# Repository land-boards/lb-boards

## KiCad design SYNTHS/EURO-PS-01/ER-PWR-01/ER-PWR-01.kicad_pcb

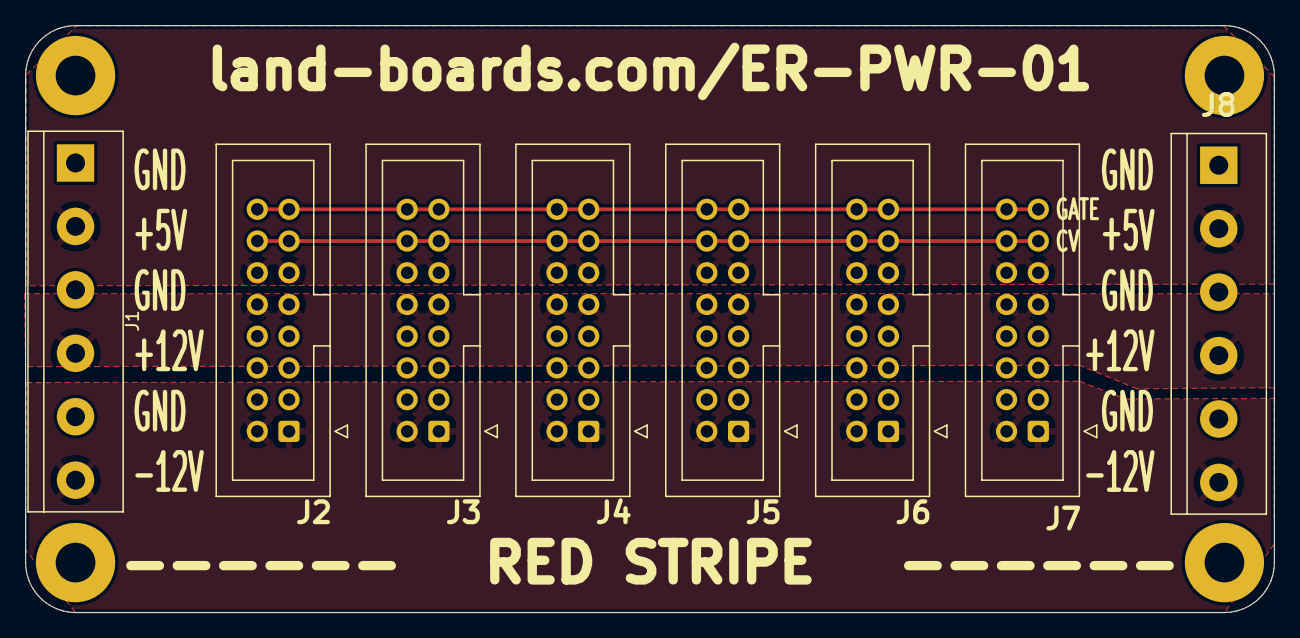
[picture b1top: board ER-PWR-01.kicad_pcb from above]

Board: 2 copper layers, 100.0 x 47.0 mm, 12 parts (0 on the bottom side), 6 nets.

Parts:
J1, J8: Conn_01x06; TerminalBlock_bornier-6_P5.08mm
J2, J3, J4, J5, J6, J7: Conn_02x08_Odd_Even; IDC-Header_2x08_P2.54mm_Vertical
MTG1, MTG2, MTG3, MTG4: MountingHole; MTG-4-40

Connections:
/+5V: J1.2, J2.11, J2.12, J3.11, J3.12, J4.11, J4.12, J5.11, J5.12, J6.11, J6.12, J7.11, J7.12, J8.2
/+12V: J1.4, J2.9, J2.10, J3.9, J3.10, J4.9, J4.10, J5.9, J5.10, J6.9, J6.10, J7.9, J7.10, J8.4
/-12V: J1.6, J2.1, J2.2, J3.1, J3.2, J4.1, J4.2, J5.1, J5.2, J6.1, J6.2, J7.1, J7.2, J8.6
/GND: J1.1, J1.3, J1.5, J2.3, J2.4, J2.5, J2.6, J2.7, J2.8, J3.3, J3.4, J3.5, J3.6, J3.7, J3.8, J4.3, J4.4, J4.5, J4.6, J4.7, J4.8, J5.3, J5.4, J5.5, J5.6, J5.7, J5.8, J6.3, J6.4, J6.5, J6.6, J6.7, J6.8, J7.3, J7.4, J7.5, J7.6, J7.7, J7.8, J8.1, J8.3, J8.5
/P13: J2.13, J2.14, J3.13, J3.14, J4.13, J4.14, J5.13, J5.14, J6.13, J6.14, J7.13, J7.14
/P15: J2.15, J2.16, J3.15, J3.16, J4.15, J4.16, J5.15, J5.16, J6.15, J6.16, J7.15, J7.16

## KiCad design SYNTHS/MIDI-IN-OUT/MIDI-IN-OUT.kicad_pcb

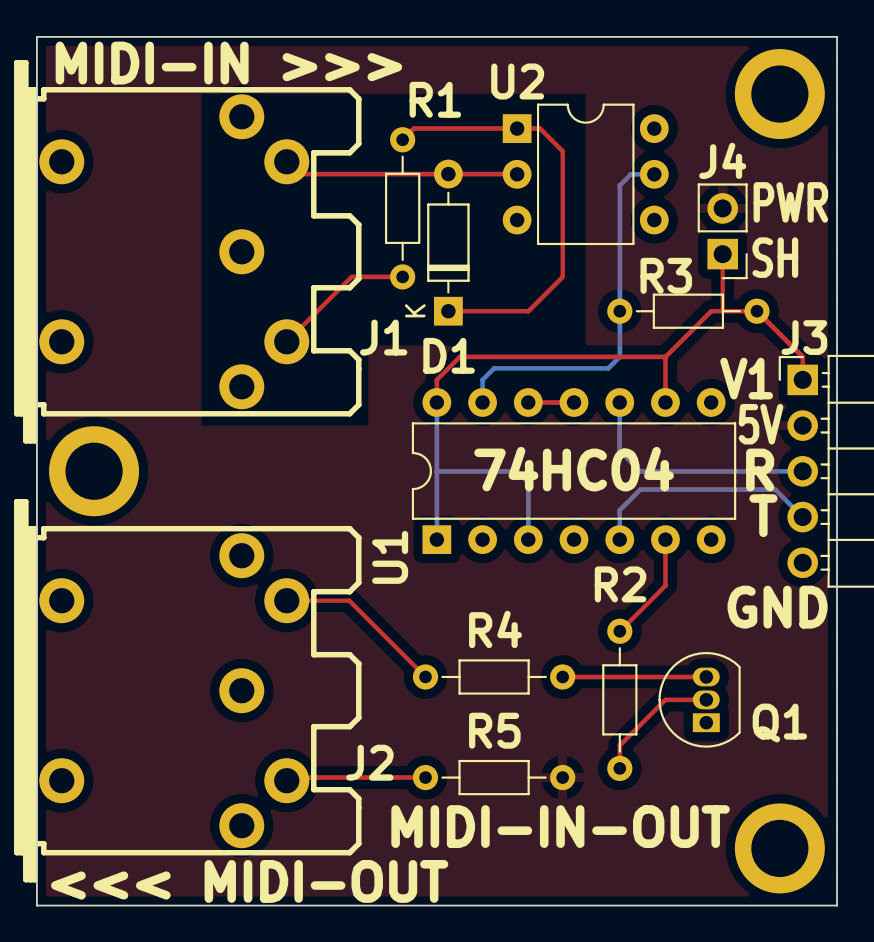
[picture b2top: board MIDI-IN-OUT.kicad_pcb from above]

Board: 2 copper layers, 44.4 x 48.3 mm, 16 parts (0 on the bottom side), 15 nets.

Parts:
D1: BAT41; D_DO-35_SOD27_P7.62mm_Horizontal
J1, J2: DIN-5; MIDI_DIN-5
J3: Conn_01x05; PinHeader_1x05_P2.54mm_Horizontal
J4: Conn_01x02; PinHeader_1x02_P2.54mm_Vertical
MTG1, MTG2, MTG3: MountingHole; MTG-4-40-SMALL
Q1: 2N3904; TO-92_Inline
R1, R4, R5: 220; R_Axial_DIN0204_L3.6mm_D1.6mm_P7.62mm_Horizontal
R2: 10K; R_Axial_DIN0204_L3.6mm_D1.6mm_P7.62mm_Horizontal
R3: 1K; R_Axial_DIN0204_L3.6mm_D1.6mm_P7.62mm_Horizontal
U1: 74HC04; DIP-14_W7.62mm
U2: 4N26; DIP-6_W7.62mm

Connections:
+3V3: J3.1, J4.1, R3.2, U1.1, U1.3, U1.9, U1.14 (VCC)
+5V: J3.2, J4.2, R5.2
/MIDI_IN: J1.4, R1.1
/RX: J3.3, U1.10
/TX: J3.4, U1.5
GND: J2.2, J3.5, Q1.1 (E), U1.7 (GND), U2.4
unnamed: D1.1 (K), R1.2, U2.1
unnamed: D1.2 (A), J1.5, U2.2
unnamed: J2.4, R5.1
unnamed: J2.5, R4.2
unnamed: Q1.2 (B), R2.1
unnamed: Q1.3 (C), R4.1
unnamed: R2.2, U1.6
unnamed: R3.1, U1.13, U2.5
unnamed: U1.11, U1.12

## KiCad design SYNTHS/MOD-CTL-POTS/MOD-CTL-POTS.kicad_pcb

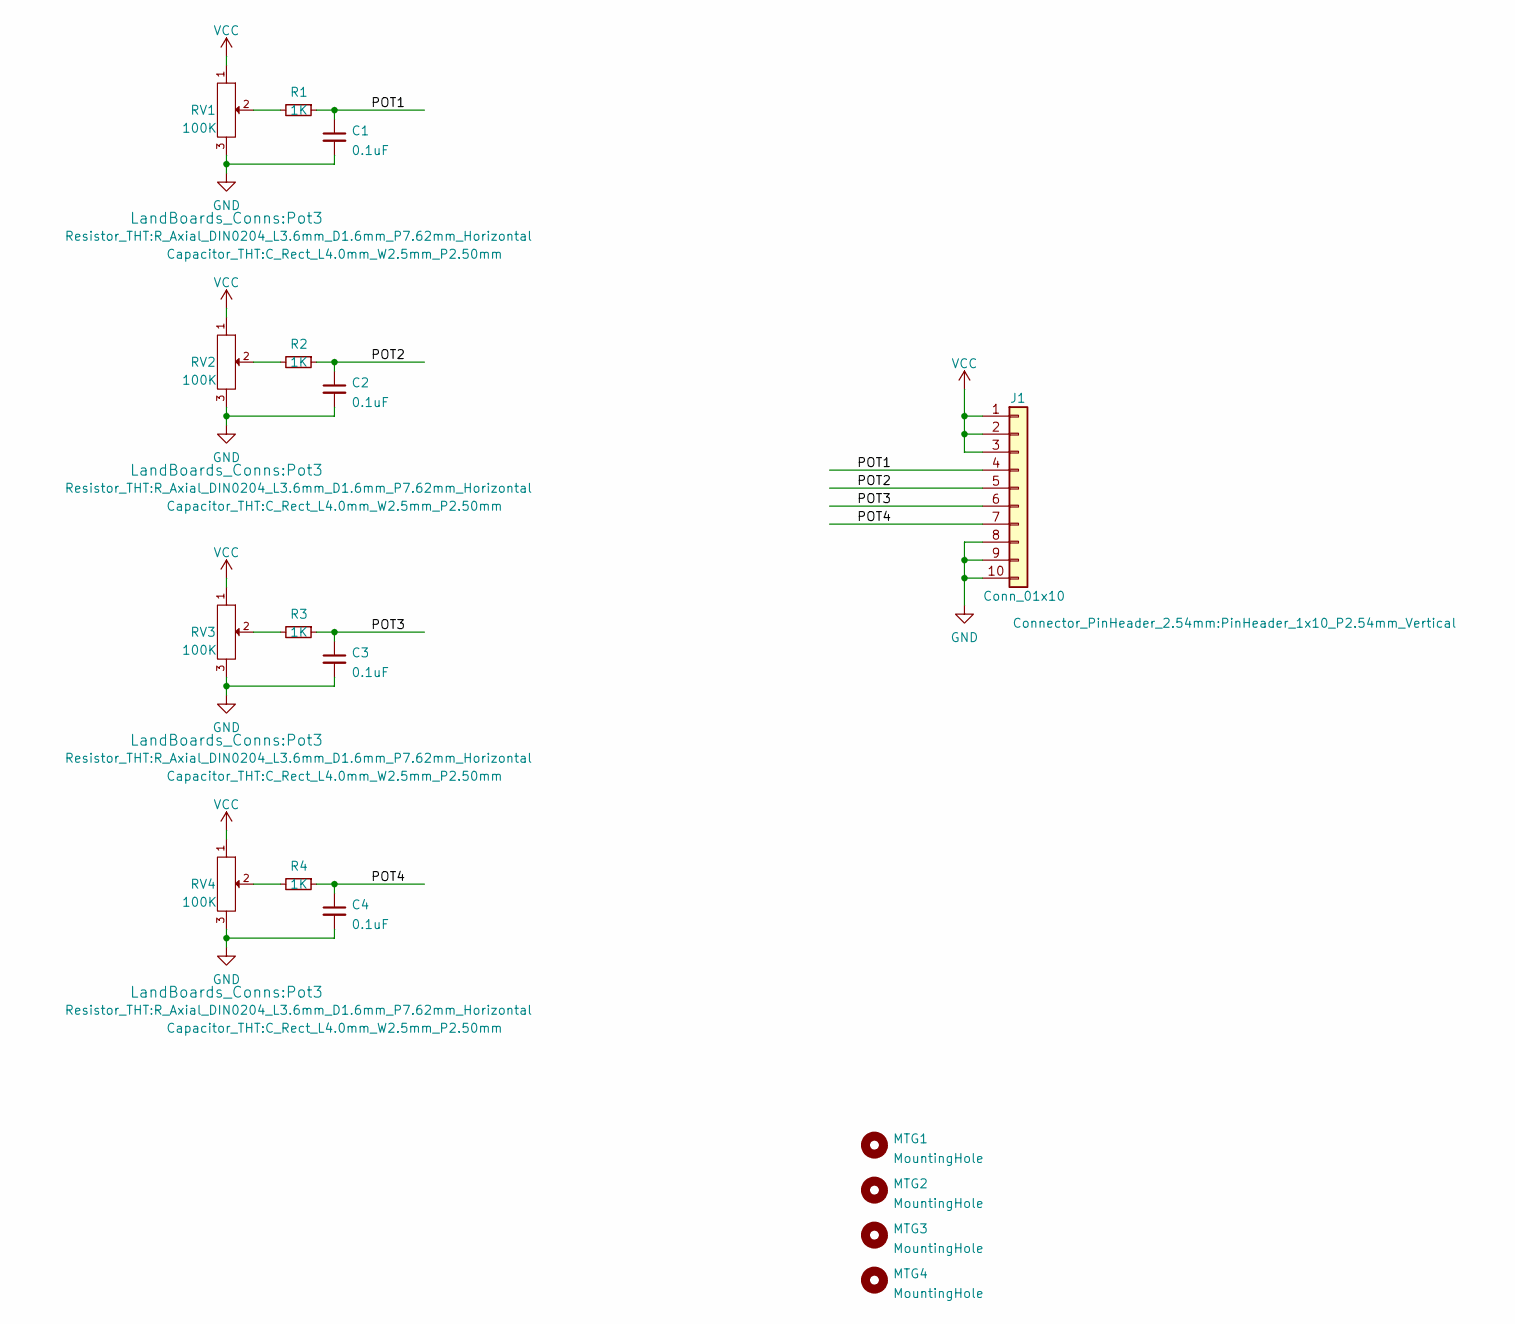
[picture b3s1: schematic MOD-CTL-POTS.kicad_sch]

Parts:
C1, C2, C3, C4: 0.1uF; C_Rect_L4.0mm_W2.5mm_P2.50mm
J1: Conn_01x10; PinHeader_1x10_P2.54mm_Vertical
MTG1, MTG2, MTG3, MTG4: MountingHole; MTG-4-40
R1, R2, R3, R4: 1K; R_Axial_DIN0204_L3.6mm_D1.6mm_P7.62mm_Horizontal
RV1, RV2, RV3, RV4: 100K; Pot3

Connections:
/POT1: C1.1, J1.4, R1.1
/POT2: C2.1, J1.5, R2.1
/POT3: C3.1, J1.6, R3.1
/POT4: C4.1, J1.7, R4.1
GND: C1.2, C2.2, C3.2, C4.2, J1.8, J1.9, J1.10, RV1.3, RV2.3, RV3.3, RV4.3
unnamed: R1.2, RV1.2
unnamed: R2.2, RV2.2
unnamed: R3.2, RV3.2
unnamed: R4.2, RV4.2
VCC: J1.1, J1.2, J1.3, RV1.1, RV2.1, RV3.1, RV4.1

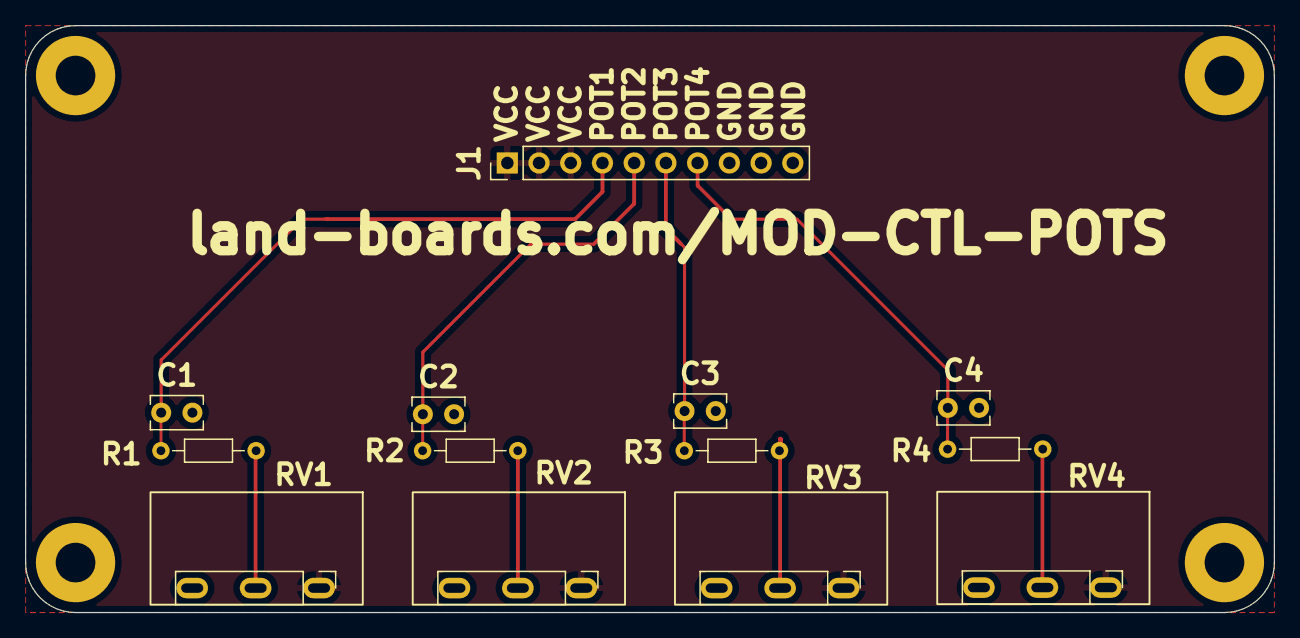
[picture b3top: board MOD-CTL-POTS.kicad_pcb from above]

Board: 2 copper layers, 100.0 x 47.0 mm, 17 parts (0 on the bottom side), 10 nets.

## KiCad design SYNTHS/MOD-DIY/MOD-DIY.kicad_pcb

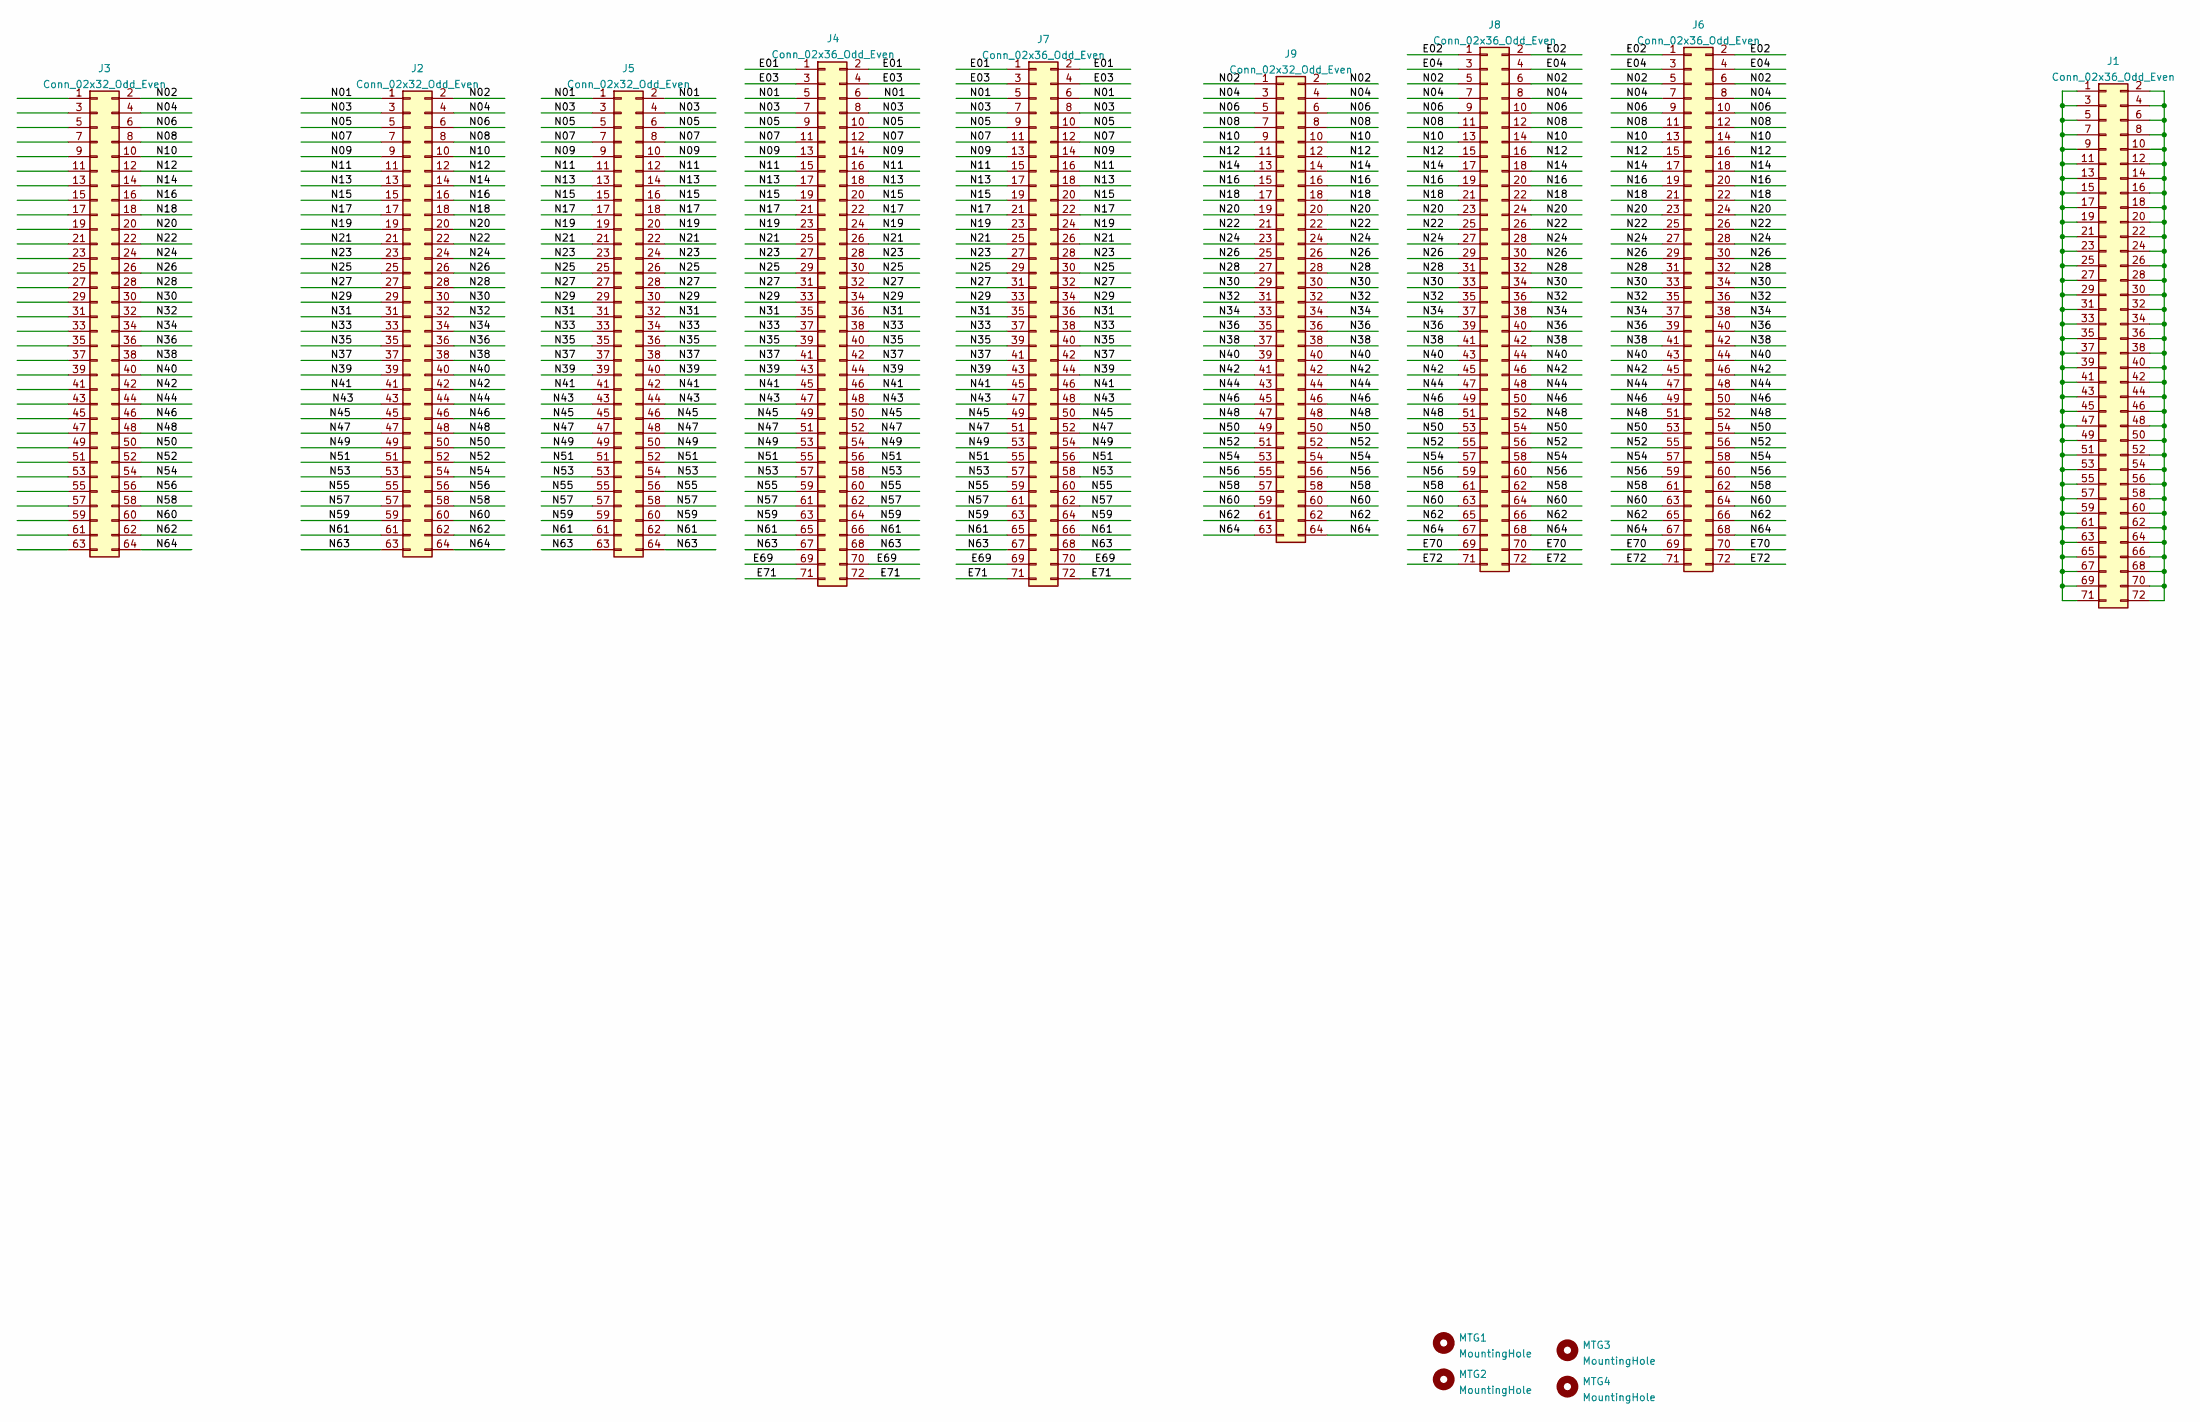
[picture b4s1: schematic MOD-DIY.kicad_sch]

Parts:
J1, J4, J6, J7, J8: Conn_02x36_Odd_Even; PinHeader_2x36_P2.54mm_Vertical
J2, J3, J5, J9: Conn_02x32_Odd_Even; PinHeader_2x32_P2.54mm_Vertical
MTG1, MTG2, MTG3, MTG4: MountingHole; MTG-4-40

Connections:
/E01: J4.1, J4.2, J7.1, J7.2
/E02: J6.1, J6.2, J8.1, J8.2
/E03: J4.3, J4.4, J7.3, J7.4
/E04: J6.3, J6.4, J8.3, J8.4
/E69: J4.69, J4.70, J7.69, J7.70
/E70: J6.69, J6.70, J8.69, J8.70
/E71: J4.71, J4.72, J7.71, J7.72
/E72: J6.71, J6.72, J8.71, J8.72
/N01: J2.1, J4.5, J4.6, J5.1, J5.2, J7.5, J7.6
/N02: J2.2, J3.2, J6.5, J6.6, J8.5, J8.6, J9.1, J9.2
/N03: J2.3, J4.7, J4.8, J5.3, J5.4, J7.7, J7.8
/N04: J2.4, J3.4, J6.7, J6.8, J8.7, J8.8, J9.3, J9.4
/N05: J2.5, J4.9, J4.10, J5.5, J5.6, J7.9, J7.10
/N06: J2.6, J3.6, J6.9, J6.10, J8.9, J8.10, J9.5, J9.6
/N07: J2.7, J4.11, J4.12, J5.7, J5.8, J7.11, J7.12
/N08: J2.8, J3.8, J6.11, J6.12, J8.11, J8.12, J9.7, J9.8
/N09: J2.9, J4.13, J4.14, J5.9, J5.10, J7.13, J7.14
/N10: J2.10, J3.10, J6.13, J6.14, J8.13, J8.14, J9.9, J9.10
/N11: J2.11, J4.15, J4.16, J5.11, J5.12, J7.15, J7.16
/N12: J2.12, J3.12, J6.15, J6.16, J8.15, J8.16, J9.11, J9.12
/N13: J2.13, J4.17, J4.18, J5.13, J5.14, J7.17, J7.18
/N14: J2.14, J3.14, J6.17, J6.18, J8.17, J8.18, J9.13, J9.14
/N15: J2.15, J4.19, J4.20, J5.15, J5.16, J7.19, J7.20
/N16: J2.16, J3.16, J6.19, J6.20, J8.19, J8.20, J9.15, J9.16
/N17: J2.17, J4.21, J4.22, J5.17, J5.18, J7.21, J7.22
/N18: J2.18, J3.18, J6.21, J6.22, J8.21, J8.22, J9.17, J9.18
/N19: J2.19, J4.23, J4.24, J5.19, J5.20, J7.23, J7.24
/N20: J2.20, J3.20, J6.23, J6.24, J8.23, J8.24, J9.19, J9.20
/N21: J2.21, J4.25, J4.26, J5.21, J5.22, J7.25, J7.26
/N22: J2.22, J3.22, J6.25, J6.26, J8.25, J8.26, J9.21, J9.22
/N23: J2.23, J4.27, J4.28, J5.23, J5.24, J7.27, J7.28
/N24: J2.24, J3.24, J6.27, J6.28, J8.27, J8.28, J9.23, J9.24
/N25: J2.25, J4.29, J4.30, J5.25, J5.26, J7.29, J7.30
/N26: J2.26, J3.26, J6.29, J6.30, J8.29, J8.30, J9.25, J9.26
/N27: J2.27, J4.31, J4.32, J5.27, J5.28, J7.31, J7.32
/N28: J2.28, J3.28, J6.31, J6.32, J8.31, J8.32, J9.27, J9.28
/N29: J2.29, J4.33, J4.34, J5.29, J5.30, J7.33, J7.34
/N30: J2.30, J3.30, J6.33, J6.34, J8.33, J8.34, J9.29, J9.30
/N31: J2.31, J4.35, J4.36, J5.31, J5.32, J7.35, J7.36
/N32: J2.32, J3.32, J6.35, J6.36, J8.35, J8.36, J9.31, J9.32
/N33: J2.33, J4.37, J4.38, J5.33, J5.34, J7.37, J7.38
/N34: J2.34, J3.34, J6.37, J6.38, J8.37, J8.38, J9.33, J9.34
/N35: J2.35, J4.39, J4.40, J5.35, J5.36, J7.39, J7.40
/N36: J2.36, J3.36, J6.39, J6.40, J8.39, J8.40, J9.35, J9.36
/N37: J2.37, J4.41, J4.42, J5.37, J5.38, J7.41, J7.42
/N38: J2.38, J3.38, J6.41, J6.42, J8.41, J8.42, J9.37, J9.38
/N39: J2.39, J4.43, J4.44, J5.39, J5.40, J7.43, J7.44
/N40: J2.40, J3.40, J6.43, J6.44, J8.43, J8.44, J9.39, J9.40
/N41: J2.41, J4.45, J4.46, J5.41, J5.42, J7.45, J7.46
/N42: J2.42, J3.42, J6.45, J6.46, J8.45, J8.46, J9.41, J9.42
/N43: J2.43, J4.47, J4.48, J5.43, J5.44, J7.47, J7.48
/N44: J2.44, J3.44, J6.47, J6.48, J8.47, J8.48, J9.43, J9.44
/N45: J2.45, J4.49, J4.50, J5.45, J5.46, J7.49, J7.50
/N46: J2.46, J3.46, J6.49, J6.50, J8.49, J8.50, J9.45, J9.46
/N47: J2.47, J4.51, J4.52, J5.47, J5.48, J7.51, J7.52
/N48: J2.48, J3.48, J6.51, J6.52, J8.51, J8.52, J9.47, J9.48
/N49: J2.49, J4.53, J4.54, J5.49, J5.50, J7.53, J7.54
/N50: J2.50, J3.50, J6.53, J6.54, J8.53, J8.54, J9.49, J9.50
/N51: J2.51, J4.55, J4.56, J5.51, J5.52, J7.55, J7.56
/N52: J2.52, J3.52, J6.55, J6.56, J8.55, J8.56, J9.51, J9.52
/N53: J2.53, J4.57, J4.58, J5.53, J5.54, J7.57, J7.58
/N54: J2.54, J3.54, J6.57, J6.58, J8.57, J8.58, J9.53, J9.54
/N55: J2.55, J4.59, J4.60, J5.55, J5.56, J7.59, J7.60
/N56: J2.56, J3.56, J6.59, J6.60, J8.59, J8.60, J9.55, J9.56
/N57: J2.57, J4.61, J4.62, J5.57, J5.58, J7.61, J7.62
/N58: J2.58, J3.58, J6.61, J6.62, J8.61, J8.62, J9.57, J9.58
/N59: J2.59, J4.63, J4.64, J5.59, J5.60, J7.63, J7.64
/N60: J2.60, J3.60, J6.63, J6.64, J8.63, J8.64, J9.59, J9.60
/N61: J2.61, J4.65, J4.66, J5.61, J5.62, J7.65, J7.66
/N62: J2.62, J3.62, J6.65, J6.66, J8.65, J8.66, J9.61, J9.62
/N63: J2.63, J4.67, J4.68, J5.63, J5.64, J7.67, J7.68
/N64: J2.64, J3.64, J6.67, J6.68, J8.67, J8.68, J9.63, J9.64
unnamed: J1.1, J1.3, J1.5, J1.7, J1.9, J1.11, J1.13, J1.15, J1.17, J1.19, J1.21, J1.23, J1.25, J1.27, J1.29, J1.31, J1.33, J1.35, J1.37, J1.39, J1.41, J1.43, J1.45, J1.47, J1.49, J1.51, J1.53, J1.55, J1.57, J1.59, J1.61, J1.63, J1.65, J1.67, J1.69, J1.71
unnamed: J1.2, J1.4, J1.6, J1.8, J1.10, J1.12, J1.14, J1.16, J1.18, J1.20, J1.22, J1.24, J1.26, J1.28, J1.30, J1.32, J1.34, J1.36, J1.38, J1.40, J1.42, J1.44, J1.46, J1.48, J1.50, J1.52, J1.54, J1.56, J1.58, J1.60, J1.62, J1.64, J1.66, J1.68, J1.70, J1.72

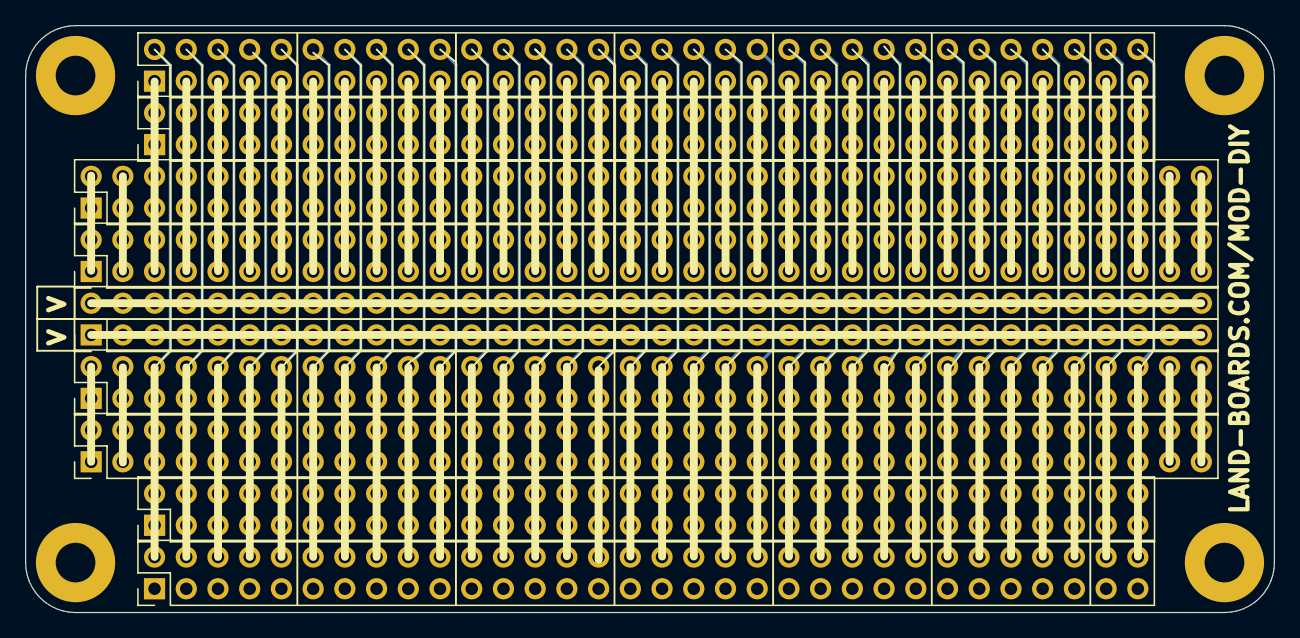
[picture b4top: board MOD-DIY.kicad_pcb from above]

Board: 2 copper layers, 100.0 x 47.0 mm, 13 parts (0 on the bottom side), 74 nets.

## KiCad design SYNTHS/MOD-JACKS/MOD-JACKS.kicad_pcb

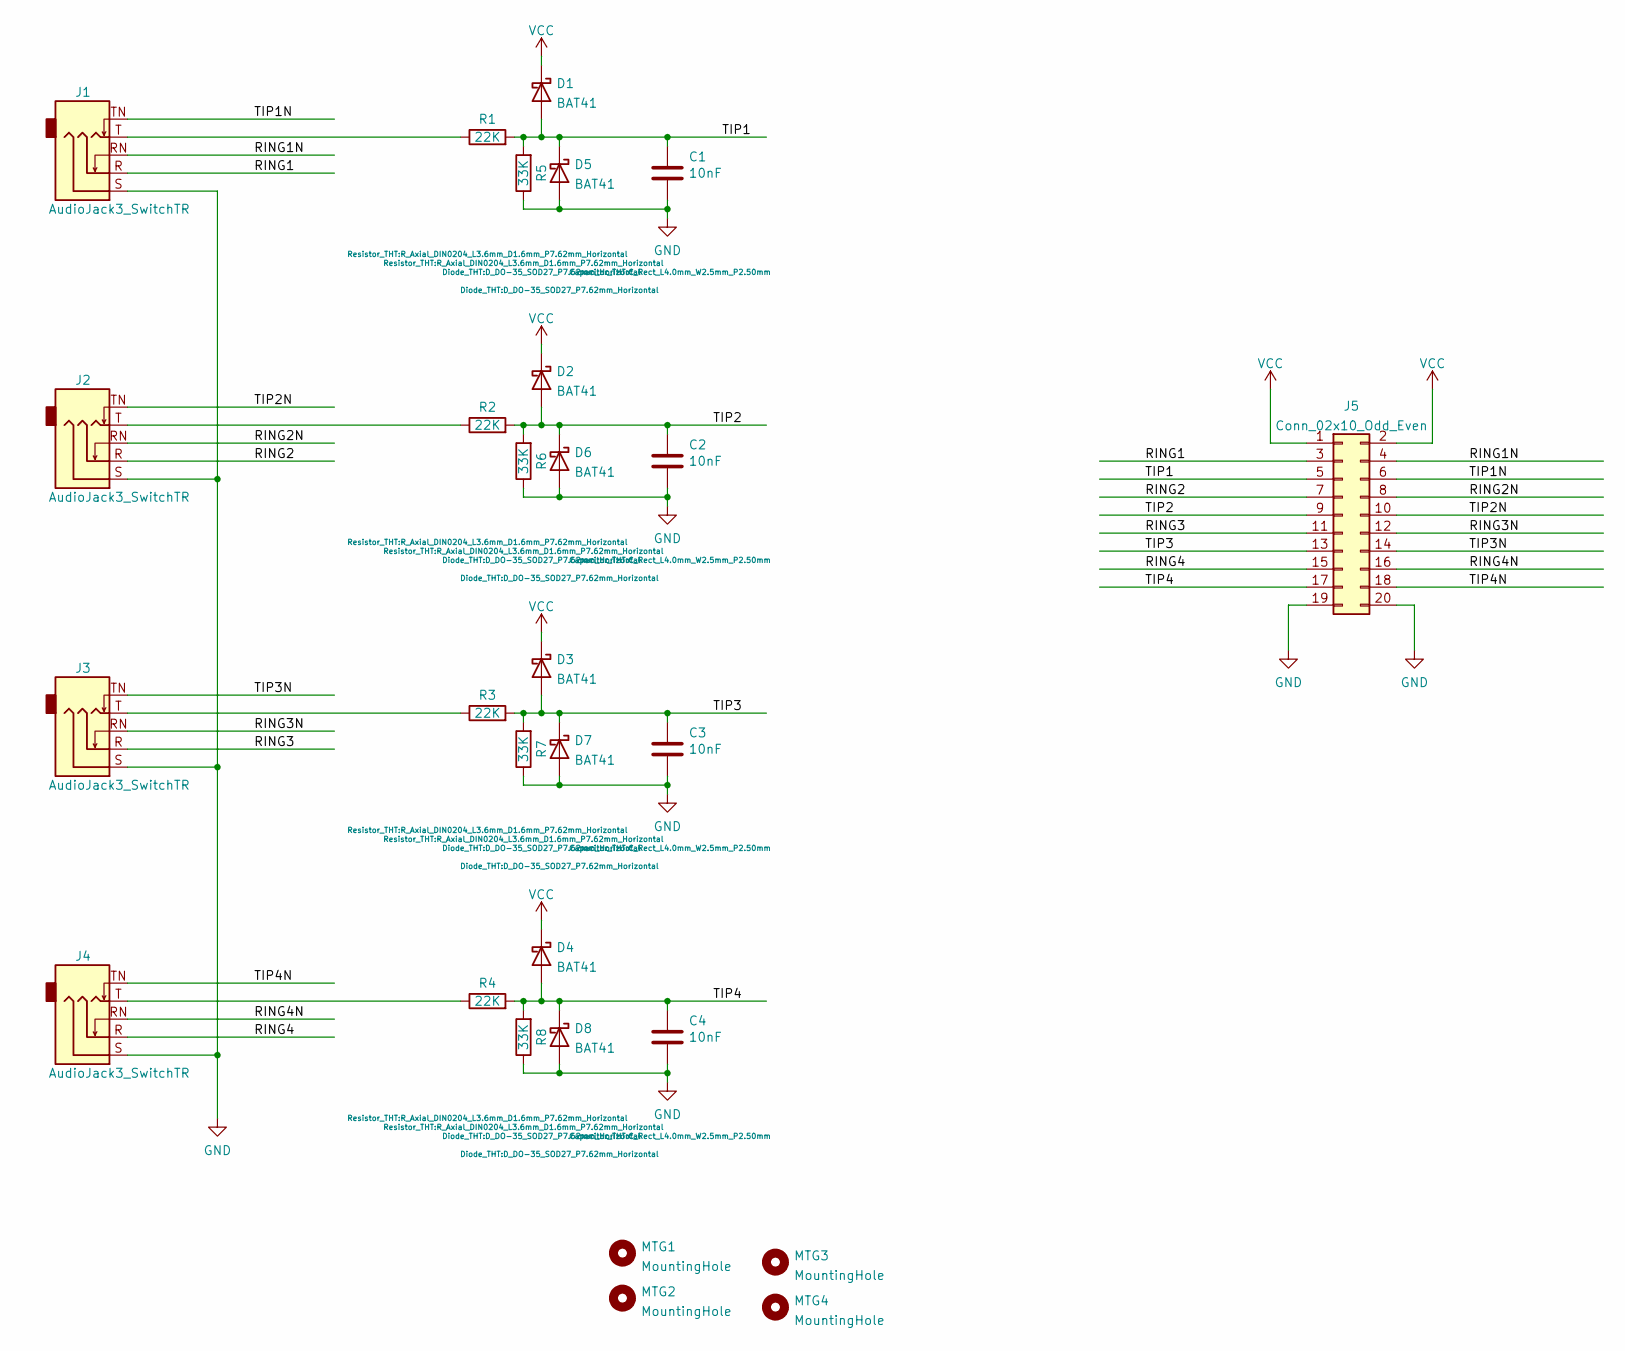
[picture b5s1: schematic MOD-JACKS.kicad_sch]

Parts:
C1, C2, C3, C4: 10nF; C_Rect_L4.0mm_W2.5mm_P2.50mm
D1, D2, D3, D4, D5, D6, D7, D8: BAT41; D_DO-35_SOD27_P7.62mm_Horizontal
J1, J2, J3, J4: AudioJack3_SwitchTR; Jack_3.5mm_CUI_SJ1-3523N_Horizontal
J5: Conn_02x10_Odd_Even; PinHeader_1x20_P2.54mm_Vertical
MTG1, MTG2, MTG3, MTG4: MountingHole; MTG-4-40
R1, R2, R3, R4: 22K; R_Axial_DIN0204_L3.6mm_D1.6mm_P7.62mm_Horizontal
R5, R6, R7, R8: 33K; R_Axial_DIN0204_L3.6mm_D1.6mm_P7.62mm_Horizontal

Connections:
/RING1: J1.R, J5.3
/RING1N: J1.RN, J5.4
/RING2: J2.R, J5.7
/RING2N: J2.RN, J5.8
/RING3: J3.R, J5.11
/RING3N: J3.RN, J5.12
/RING4: J4.R, J5.15
/RING4N: J4.RN, J5.16
/TIP1: C1.1, D1.2 (A), D5.1 (K), J5.5, R1.2, R5.2
/TIP1N: J1.TN, J5.6
/TIP2: C2.1, D2.2 (A), D6.1 (K), J5.9, R2.2, R6.2
/TIP2N: J2.TN, J5.10
/TIP3: C3.1, D3.2 (A), D7.1 (K), J5.13, R3.2, R7.2
/TIP3N: J3.TN, J5.14
/TIP4: C4.1, D4.2 (A), D8.1 (K), J5.17, R4.2, R8.2
/TIP4N: J4.TN, J5.18
GND: C1.2, C2.2, C3.2, C4.2, D5.2 (A), D6.2 (A), D7.2 (A), D8.2 (A), J1.S, J2.S, J3.S, J4.S, J5.19, J5.20, R5.1, R6.1, R7.1, R8.1
unnamed: J1.T, R1.1
unnamed: J2.T, R2.1
unnamed: J3.T, R3.1
unnamed: J4.T, R4.1
VCC: D1.1 (K), D2.1 (K), D3.1 (K), D4.1 (K), J5.1, J5.2

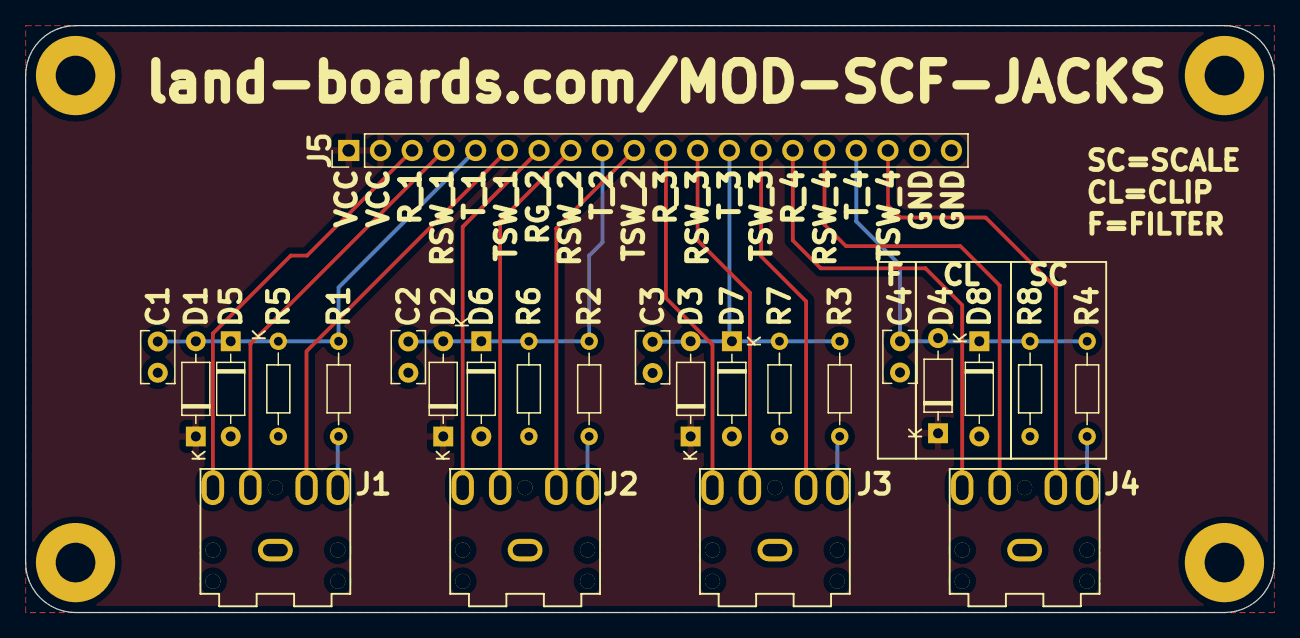
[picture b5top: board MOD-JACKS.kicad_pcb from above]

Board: 2 copper layers, 100.0 x 47.0 mm, 29 parts (0 on the bottom side), 22 nets.

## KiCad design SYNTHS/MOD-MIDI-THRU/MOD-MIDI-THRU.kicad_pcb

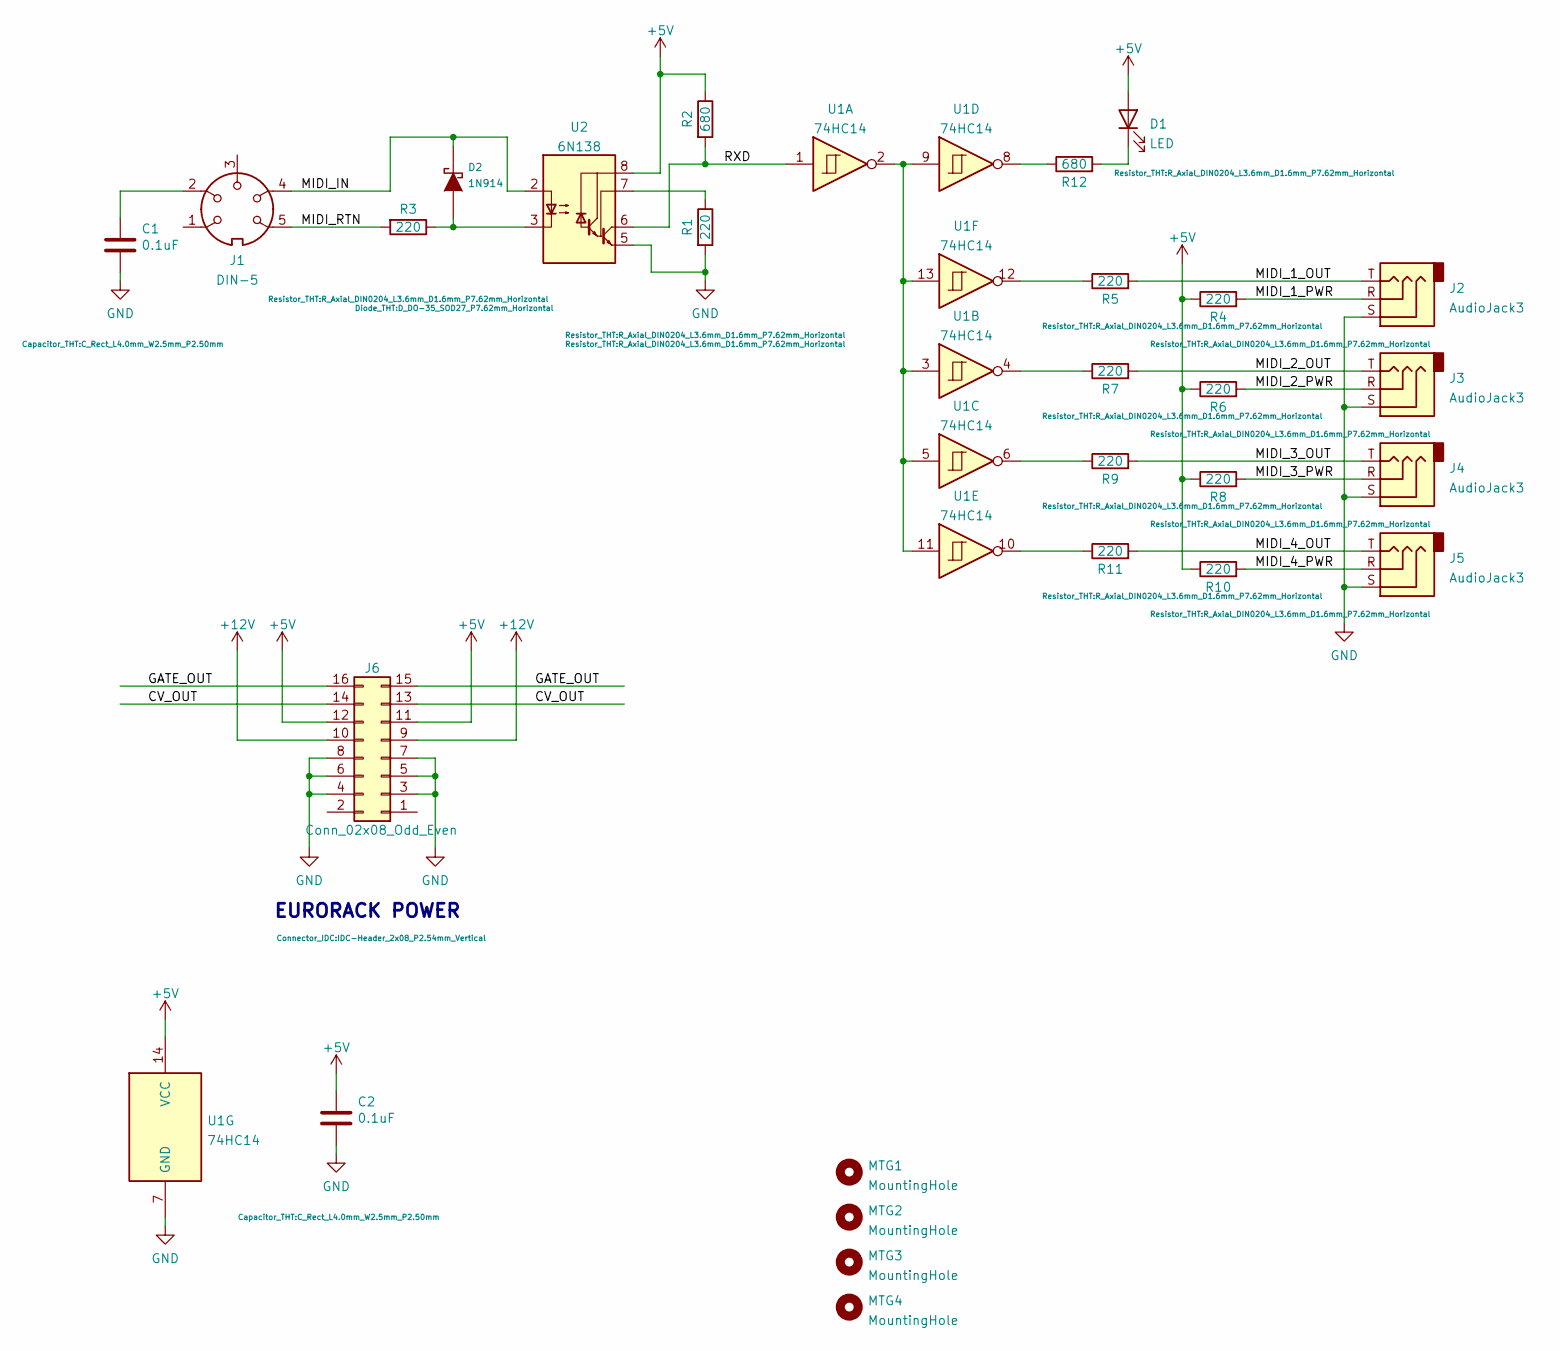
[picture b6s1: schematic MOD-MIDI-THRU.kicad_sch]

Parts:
C1, C2: 0.1uF; C_Rect_L4.0mm_W2.5mm_P2.50mm
D1: LED; LED_D5.0mm
D2: 1N914; D_DO-35_SOD27_P7.62mm_Horizontal
J1: DIN-5; MIDI_DIN-5
J2, J3, J4, J5: AudioJack3; Jack_3.5mm_CUI_SJ1-3523N_Horizontal
J6: Conn_02x08_Odd_Even; IDC-Header_2x08_P2.54mm_Vertical
MTG1, MTG2, MTG3, MTG4: MountingHole; MTG-4-40
R1, R3, R4, R5, R6, R7, R8, R9, R10, R11: 220; R_Axial_DIN0204_L3.6mm_D1.6mm_P7.62mm_Horizontal
R2, R12: 680; R_Axial_DIN0204_L3.6mm_D1.6mm_P7.62mm_Horizontal
U1: 74HC14; DIP-14_W7.62mm_LongPads
U2: 6N138; DIP-8_W7.62mm_Socket_LongPads

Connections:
+5V: C2.1, D1.2 (A), J6.11, J6.12, R2.1, R4.1, R6.1, R8.1, R10.1, U1.14 (VCC), U2.8 (VCC)
+12V: J6.9, J6.10
/CV_OUT: J6.13, J6.14
/GATE_OUT: J6.15, J6.16
/MIDI_1_OUT: J2.T, R5.2
/MIDI_1_PWR: J2.R, R4.2
/MIDI_2_OUT: J3.T, R7.2
/MIDI_2_PWR: J3.R, R6.2
/MIDI_3_OUT: J4.T, R9.2
/MIDI_3_PWR: J4.R, R8.2
/MIDI_4_OUT: J5.T, R11.2
/MIDI_4_PWR: J5.R, R10.2
/MIDI_IN: D2.1 (K), J1.4, U2.2 (C1)
/MIDI_RTN: J1.5, R3.2
/RXD: R2.2, U1.1, U2.6 (VO2)
GND: C1.2, C2.2, J2.S, J3.S, J4.S, J5.S, J6.3, J6.4, J6.5, J6.6, J6.7, J6.8, R1.2, U1.7 (GND), U2.5 (GND)
unnamed: C1.1, J1.2
unnamed: D1.1 (K), R12.2
unnamed: D2.2 (A), R3.1, U2.3 (C2)
unnamed: R1.1, U2.7 (VO1)
unnamed: R5.1, U1.12
unnamed: R7.1, U1.4
unnamed: R9.1, U1.6
unnamed: R11.1, U1.10
unnamed: R12.1, U1.8
unnamed: U1.2, U1.3, U1.5, U1.9, U1.11, U1.13

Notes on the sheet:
EURORACK POWER

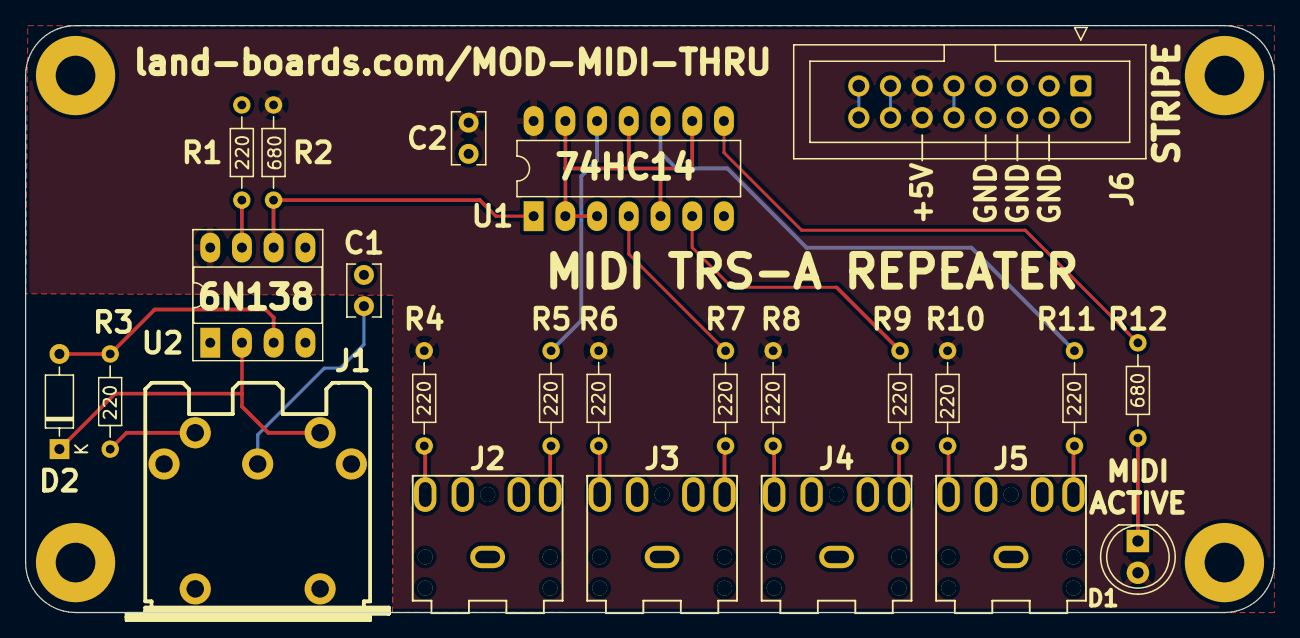
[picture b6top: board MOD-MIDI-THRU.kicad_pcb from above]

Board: 2 copper layers, 100.0 x 47.0 mm, 28 parts (0 on the bottom side), 26 nets.
